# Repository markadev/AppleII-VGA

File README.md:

# Apple II VGA Card

This project is a VGA card for Apple II computers to ouput a crisp RGB signal to a
VGA monitor instead of having to rely on the composite output. This is accomplished
by snooping the 6502 bus and creating a shadow copy of the video memory within a
Raspberry Pi Pico, then processing the raw video memory contents to output a "perfect"
signal.

    +------+                +-----+      +-----------+
    | 6502 |________________| RAM |______| Composite | 
    | CPU  |  System   \    +-----+      | Video Gen |
    +------+   Bus     |                 +-----------+
                       |    +-----------+
                       \____| Raspberry |_________________\
                            |  Pi Pico  |   640x480 VGA   /
                            +-----------+

These features are currently supported:
 * Generates a 640x480@60 VGA signal with 3 bits per color channel using resistor DACs
 * Text mode (monochrome)
 * Lo-res mode with no color fringing between the chunky pixels
 * Hi-res mode with simulated NTSC artifact color
 * Mixed lo-res and hi-res modes with monochrome text and no color fringing
 * Apple IIe video modes: 80-column text, double-lores, & double-hires
   (thanks to @dkgrizzly and @Paco1979)
 * Soft-monochrome mode to force display as if on a monochrome monitor
 * Some Video-7 RGB card extended graphical modes are implemented
 * Compatibility with Videx VideoTerm modes on Apple II+ (thanks to @abaffa)

I had these goals in mind during design:
 * Generate video out to a more modern display - I don't have any old CRTs for
   displaying composite signals any more and composite to HDMI adapters don't work well.
 * Generate crisp video - I wanted "perfect" video output, the way that it should have
   been barring technical difficulties of displays in 1980. So like, no NTSC artifact
   coloring where it's not supposed to be.
 * Non-invasive - I didn't want to have to solder or modify my logic board.
 * Common parts - The parts to build should be cheap and easy to get anywhere,
   just like the original Apple II
 * Open-source - If this helps anyone else make their Apple II better then that's
   a bonus.

I also wanted to see if a Pi Pico could actually work on an 8-bit CPU bus, since the docs
say it should work but there were no code examples.

## Project Status

This is currently a DIY project that several folks have built on their own, ranging from
[hand-wired prototype boards](docs/prototype_card.jpg) to
[custom](https://user-images.githubusercontent.com/7944844/243266290-d05ce815-0a3d-4464-a4da-49dd44d71e92.jpg)
[PCBs](https://user-images.githubusercontent.com/94628/253134471-0d5ad359-75ae-400a-acfa-885c80c36e78.jpg)
and run in their Apple II+'s and IIe's. I consider it to be pretty stable at this point.

Included in this repo are:
 * The main expansion board [KiCad Project](AppleVGA/), [Schematics](AppleVGA/AppleVGA.pdf),
   [BOM](AppleVGA/AppleVGA_BOM.csv), and [Gerber files](AppleVGA/outputs/)
 * An optional connector board [KiCad Project](AppleVGA-Connector/),
   [Schematics](AppleVGA-Connector/AppleVGA-Connector.pdf),
   [BOM](AppleVGA-Connector/AppleVGA-Connector_BOM.csv),
   and [Gerber files](AppleVGA-Connector/outputs/). (You could also build a custom cable instead)
 * The [source code for the Pi Pico microcontroller](pico/)

If you're going to build a card then check the [assembly guide](docs/Assembly.md) and
[hardware changelog](AppleVGA/CHANGELOG.txt) for important notes.

Many thanks go to the folks in the Discussion area to help push this project forward with bug
fixes & reports, and design ideas!

**Main board**

**Connector board**
_thanks to @swetland for [this idea](https://github.com/markadev/AppleII-VGA/discussions/15#discussioncomment-6432841)_

**In the wild**

## Comparisons

Here are a few comparisons of the VGA card output vs composite video through
a cheap composite -> HDMI adapter

**Text**

**Lores**

**Hires**

**DHires**

**80 Columns**

## 80 Column support for the Apple II+

The firmware implements Videx VideoTerm compatibility when there's a VideoTerm card installed
in slot 3. It's not enabled by default but if you have a Videx VideoTerm card in slot 3
then you can enable 80 column VGA support using the Configuration Disk image. The VGA card
can still be installed in any slot.

**Apple II+ running 80 Columns Examples**

## Future work

With the Rev B hardware design, the firmware has access to the Apple bus' SYNC signal
when installed in slot 7. Theoretically the firmware could synchronize the VGA display
scans with the video hardware in the Apple II.

Though possible, it looks like it would be a large overhaul to implement this synchronization
and I've found no real-world use for it so I don't plan on completing this functionality.

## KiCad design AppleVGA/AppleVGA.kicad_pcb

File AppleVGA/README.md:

# AppleII-VGA expansion card

Requirements:
  - KiCad 8.0 or later

This project uses additional KiCad libraries:
 - https://github.com/ncarandini/KiCad-RP-Pico

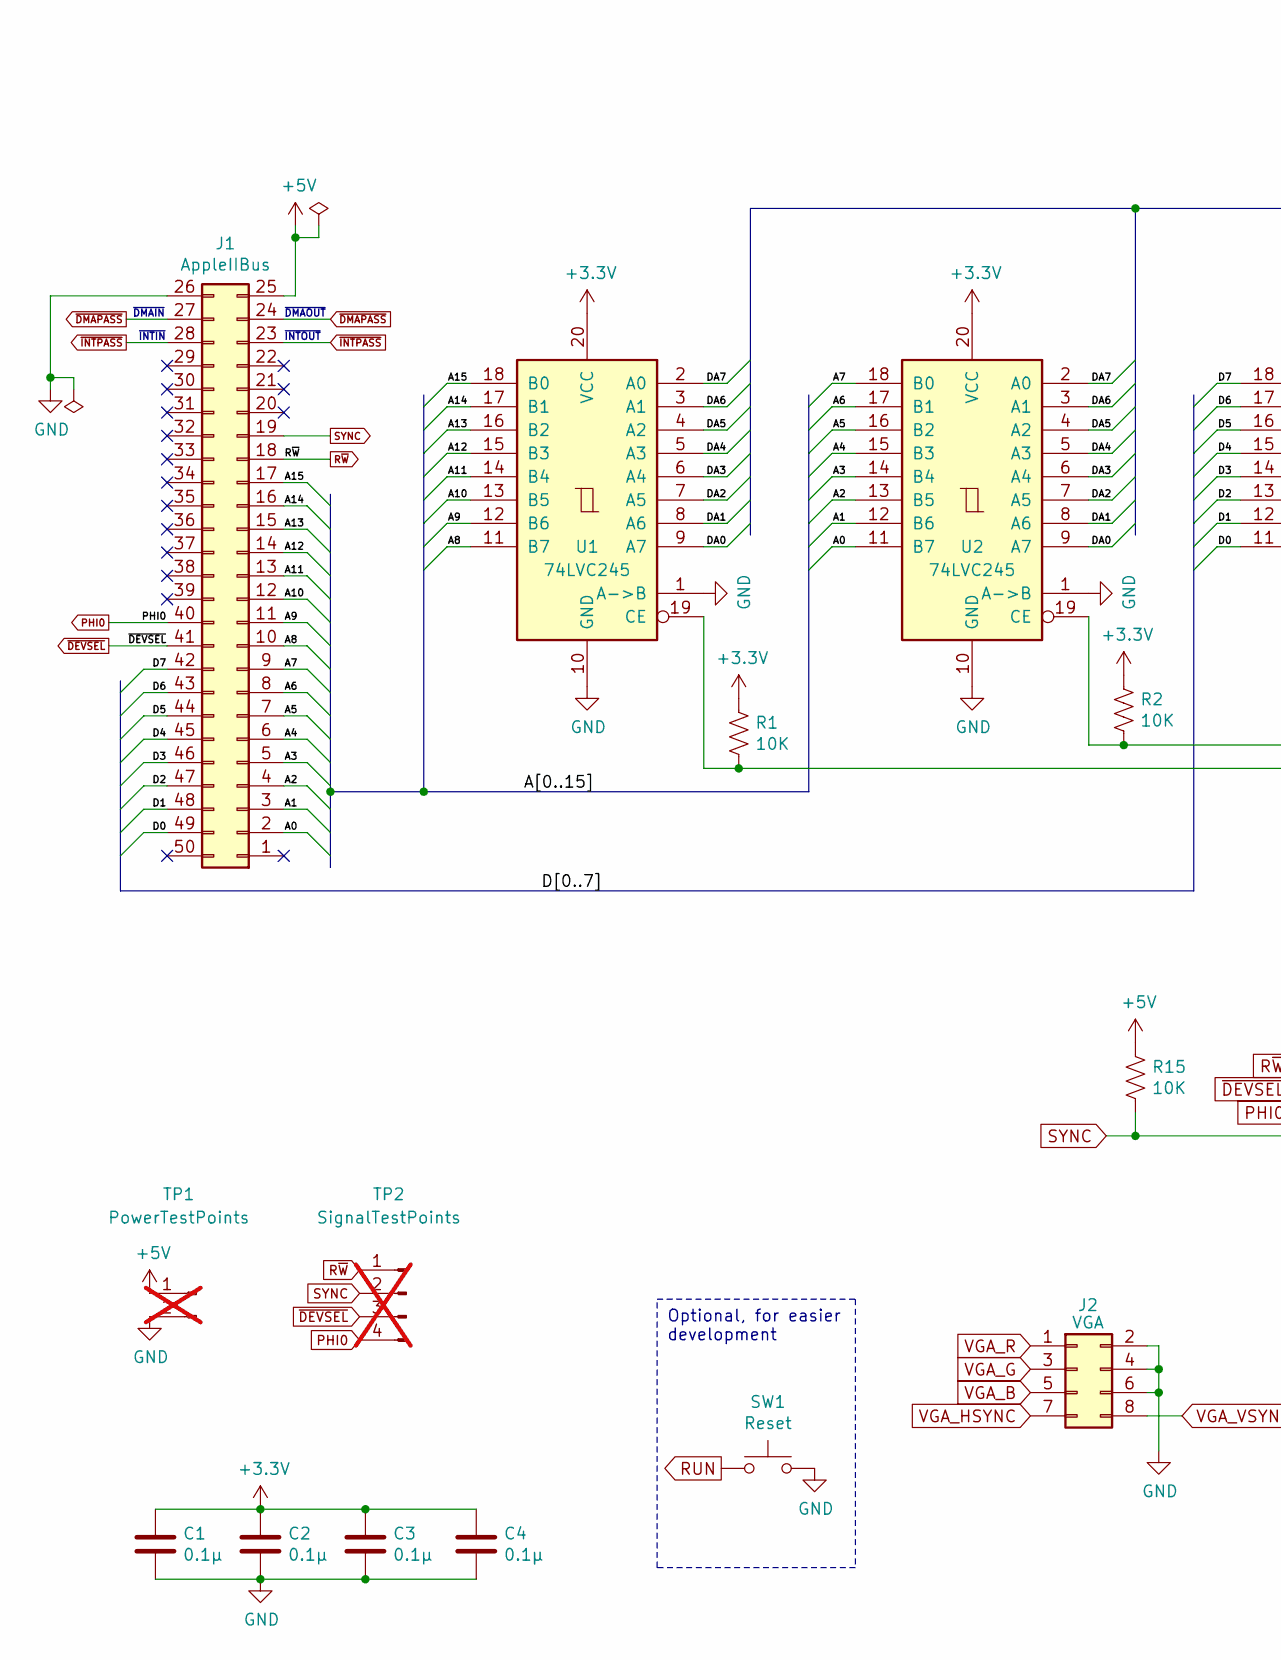
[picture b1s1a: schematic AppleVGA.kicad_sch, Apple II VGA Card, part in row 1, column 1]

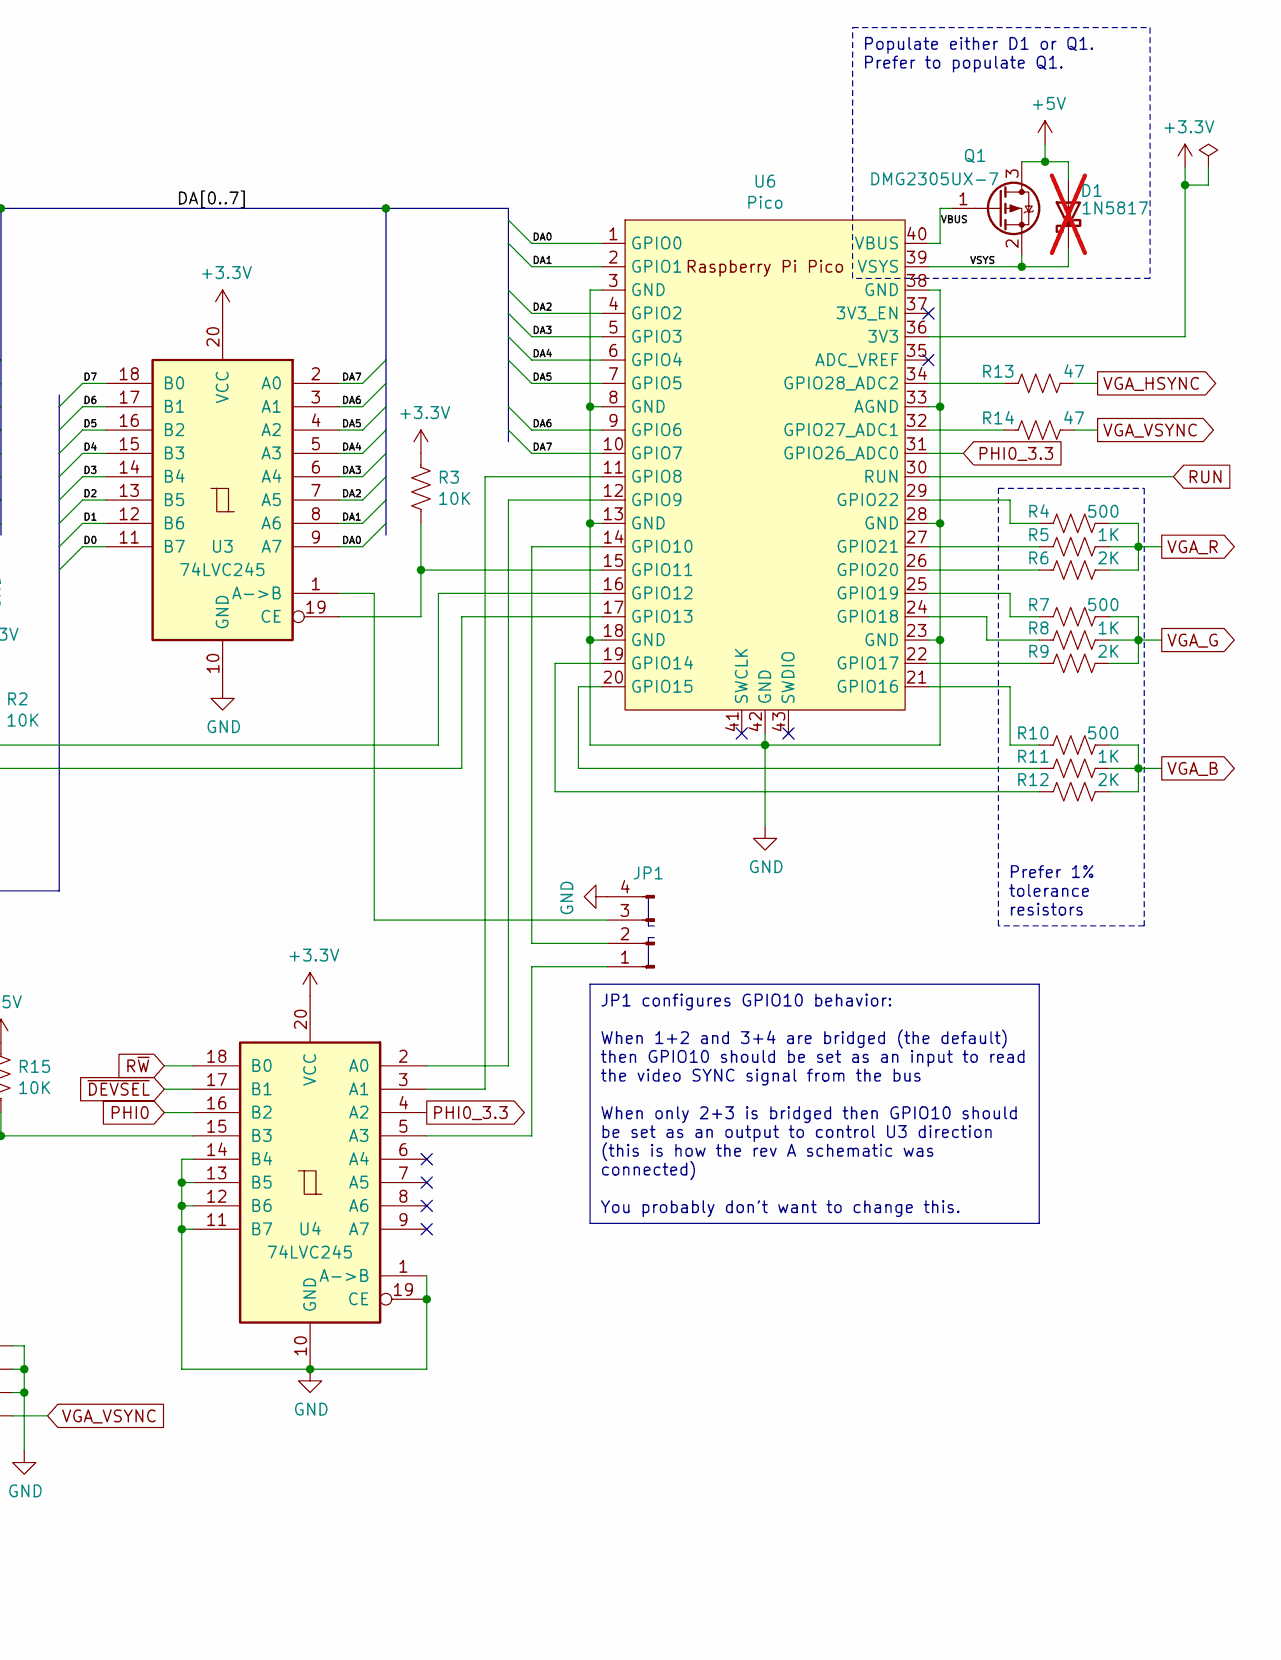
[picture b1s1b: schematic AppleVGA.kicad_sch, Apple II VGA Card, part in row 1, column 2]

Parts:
C1, C2, C3, C4: 0.1μ; C_Disc_D4.3mm_W1.9mm_P5.00mm; MouserNo 594-A104K15X7RF5TAA
D1: 1N5817; D_DO-41_SOD81_P10.16mm_Horizontal; MouserNo 511-1N5817; not fitted
J1: AppleIIBus; AppleIIBus_Edge
J2: VGA; IDC-Header_2x04_P2.54mm_Vertical; MouserNo 649-75869-232LF
JP1: JumperPads; SolderJumper-4_P1.3mm_Bridged12_34_RoundedPad1.0x1.5mm_Numb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
Q1: DMG2305UX-7; SOT-23; MouserNo 621-DMG2305UX-7
R1, R2, R3, R15: 10K; R_Axial_DIN0207_L6.3mm_D2.5mm_P10.16mm_Thin_Horizontal; MouserNo 603-CFR-25JR-5210K
R4, R7, R10: 500; R_Axial_DIN0207_L6.3mm_D2.5mm_P10.16mm_Thin_Horizontal; MouserNo 603-MFR-25FBF52-499R
R5, R8, R11: 1K; R_Axial_DIN0207_L6.3mm_D2.5mm_P10.16mm_Thin_Horizontal; MouserNo 603-MFR-25FBF52-1K
R6, R9, R12: 2K; R_Axial_DIN0207_L6.3mm_D2.5mm_P10.16mm_Thin_Horizontal; MouserNo 603-MFR-25FBF52-2K
R13, R14: 47; R_Axial_DIN0207_L6.3mm_D2.5mm_P10.16mm_Thin_Horizontal; MouserNo 603-MFR-25FTF52-47R
SW1: Reset; SW_PUSH_6mm_H5mm; MouserNo 506-FSM4JH
TP1: PowerTestPoints; PinHeader_1x02_P2.54mm_Vertical; not fitted
TP2: SignalTestPoints; PinHeader_1x04_P2.54mm_Vertical; not fitted
U1, U2, U3, U4: 74LVC245; DIP-20_W7.62mm_Socket; MouserNo 595-SN74LVC245AN
U6: Pico; RPi_Pico_SMD_TH

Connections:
+3.3V: C1.1, C2.1, C3.1, C4.1, R1.1, R2.1, R3.1, U1.20 (VCC), U2.20 (VCC), U3.20 (VCC), U4.20 (VCC), U6.36 (3V3)
+5V: D1.2 (A), J1.25, Q1.3 (D), R15.1, TP1.1
/A0: J1.2, U2.11 (B7)
/A1: J1.3, U2.12 (B6)
/A2: J1.4, U2.13 (B5)
/A3: J1.5, U2.14 (B4)
/A4: J1.6, U2.15 (B3)
/A5: J1.7, U2.16 (B2)
/A6: J1.8, U2.17 (B1)
/A7: J1.9, U2.18 (B0)
/A8: J1.10, U1.11 (B7)
/A9: J1.11, U1.12 (B6)
/A10: J1.12, U1.13 (B5)
/A11: J1.13, U1.14 (B4)
/A12: J1.14, U1.15 (B3)
/A13: J1.15, U1.16 (B2)
/A14: J1.16, U1.17 (B1)
/A15: J1.17, U1.18 (B0)
/D0: J1.49, U3.11 (B7)
/D1: J1.48, U3.12 (B6)
/D2: J1.47, U3.13 (B5)
/D3: J1.46, U3.14 (B4)
/D4: J1.45, U3.15 (B3)
/D5: J1.44, U3.16 (B2)
/D6: J1.43, U3.17 (B1)
/D7: J1.42, U3.18 (B0)
/DA0: U1.9 (A7), U2.9 (A7), U3.9 (A7), U6.1 (GPIO0)
/DA1: U1.8 (A6), U2.8 (A6), U3.8 (A6), U6.2 (GPIO1)
/DA2: U1.7 (A5), U2.7 (A5), U3.7 (A5), U6.4 (GPIO2)
/DA3: U1.6 (A4), U2.6 (A4), U3.6 (A4), U6.5 (GPIO3)
/DA4: U1.5 (A3), U2.5 (A3), U3.5 (A3), U6.6 (GPIO4)
/DA5: U1.4 (A2), U2.4 (A2), U3.4 (A2), U6.7 (GPIO5)
/DA6: U1.3 (A1), U2.3 (A1), U3.3 (A1), U6.9 (GPIO6)
/DA7: U1.2 (A0), U2.2 (A0), U3.2 (A0), U6.10 (GPIO7)
/VBUS: Q1.1 (G), U6.40 (VBUS)
/VSYS: D1.1 (K), Q1.2 (S), U6.39 (VSYS)
GND: C1.2, C2.2, C3.2, C4.2, J1.26, J2.2, J2.4, J2.6, JP1.4, SW1.2, TP1.2, U1.1 (A->B), U1.10 (GND), U2.1 (A->B), U2.10 (GND), U3.10 (GND), U4.1 (A->B), U4.10 (GND), U4.11 (B7), U4.12 (B6), U4.13 (B5), U4.14 (B4), U4.19 (CE), U6.3 (GND), U6.8 (GND), U6.13 (GND), U6.18 (GND), U6.23 (GND), U6.28 (GND), U6.33 (AGND), U6.38 (GND), U6.42 (GND)
unnamed: JP1.1, U4.5 (A3)
unnamed: JP1.2, U6.14 (GPIO10)
unnamed: JP1.3, U3.1 (A->B)
unnamed: R1.2, U1.19 (CE), U6.17 (GPIO13)
unnamed: R2.2, U2.19 (CE), U6.16 (GPIO12)
unnamed: R3.2, U3.19 (CE), U6.15 (GPIO11)
unnamed: U4.2 (A0), U6.12 (GPIO9)
unnamed: U4.3 (A1), U6.11 (GPIO8)
unnamed: R12.1, U6.19 (GPIO14)
unnamed: R11.1, U6.20 (GPIO15)
unnamed: R10.1, U6.21 (GPIO16)
unnamed: R9.1, U6.22 (GPIO17)
unnamed: R8.1, U6.24 (GPIO18)
unnamed: R7.1, U6.25 (GPIO19)
unnamed: R6.1, U6.26 (GPIO20)
unnamed: R5.1, U6.27 (GPIO21)
unnamed: R4.1, U6.29 (GPIO22)
unnamed: R14.1, U6.32 (GPIO27_ADC1)
unnamed: R13.1, U6.34 (GPIO28_ADC2)
PHI0: J1.40, TP2.4, U4.16 (B2)
PHI0_3.3: U4.4 (A2), U6.31 (GPIO26_ADC0)
RUN: SW1.1, U6.30 (RUN)
R~W: J1.18, TP2.1, U4.18 (B0)
SYNC: J1.19, R15.2, TP2.2, U4.15 (B3)
VGA_B: J2.5, R10.2, R11.2, R12.2
VGA_G: J2.3, R7.2, R8.2, R9.2
VGA_HSYNC: J2.7, R13.2
VGA_R: J2.1, R4.2, R5.2, R6.2
VGA_VSYNC: J2.8, R14.2
~DEVSEL: J1.41, TP2.3, U4.17 (B1)
~DMAPASS: J1.24, J1.27
~INTPASS: J1.23, J1.28

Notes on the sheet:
Optional, for easier development
Populate either D1 or Q1. Prefer to populate Q1.
JP1 configures GPIO10 behavior: When 1+2 and 3+4 are bridged (the default) then GPIO10 should be set as an input to read the video SYNC signal from the bus When only 2+3 is bridged then GPIO10 should be set as an output to control U3 direction (this is how the rev A schematic was connected) You pro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
Prefer 1% tolerance resistors
~{DMAIN}
~{INTOUT}
~{DMAOUT}
~{INTIN}

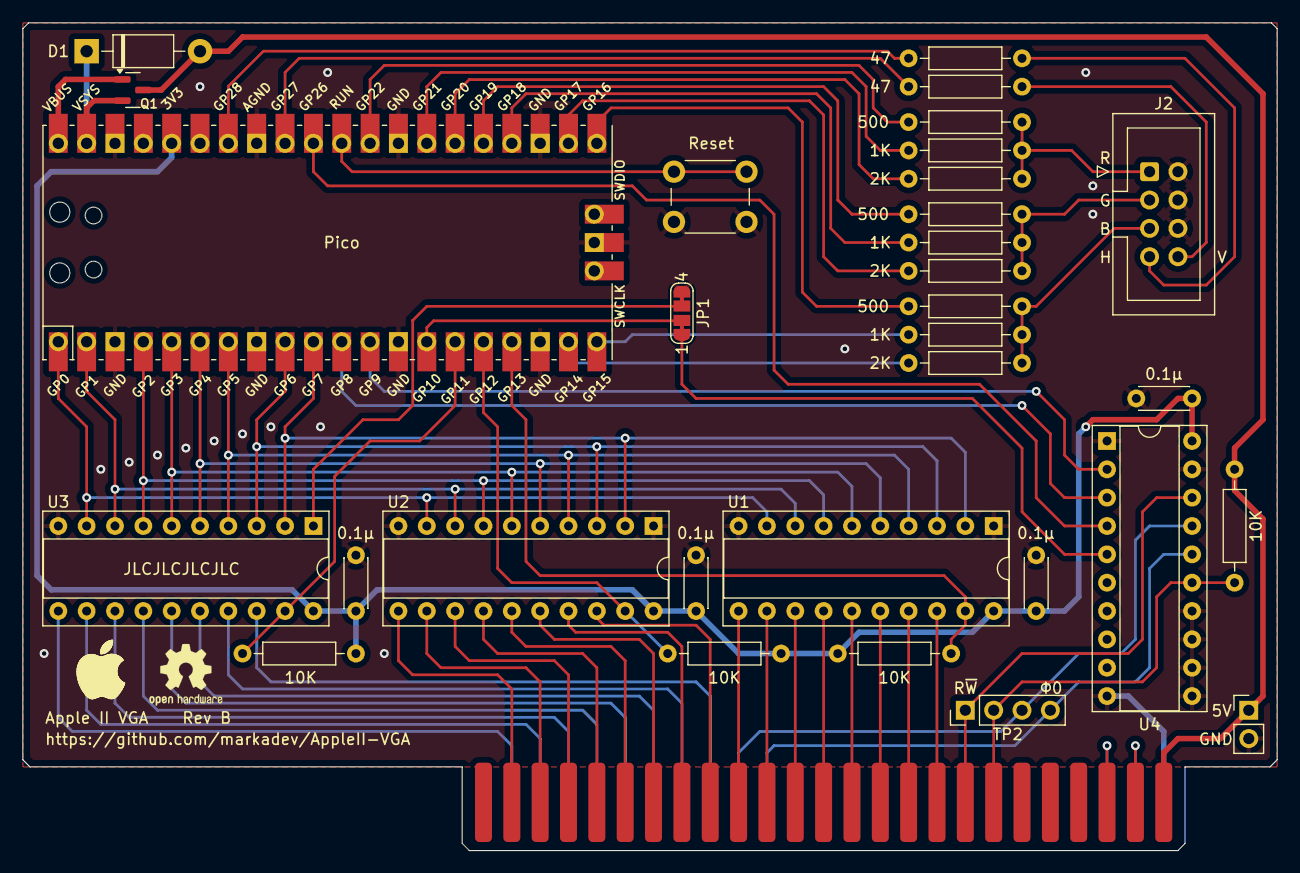
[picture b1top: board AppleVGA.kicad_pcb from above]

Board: 2 copper layers, 112.4 x 74.2 mm, 33 parts (0 on the bottom side), 69 nets.

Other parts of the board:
LOGO1: AppleLogo_5mm

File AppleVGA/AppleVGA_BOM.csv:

"#","Reference","Qty","Value","Footprint","DNP","Mfr","MfrNo","MouserNo"
"1","C1, C2, C3, C4","4","0.1μ","Capacitor_THT:C_Disc_D4.3mm_W1.9mm_P5.00mm","","","","594-A104K15X7RF5TAA"
"2","D1","1","1N5817","Diode_THT:D_DO-41_SOD81_P10.16mm_Horizontal","DNP","STMicroelectronics","1N5817","511-1N5817"
"3","J2","1","VGA","Connector_IDC:IDC-Header_2x04_P2.54mm_Vertical","","","","649-75869-232LF"
"4","Q1","1","DMG2305UX-7","Package_TO_SOT_SMD:SOT-23","","Diodes Incorporated","DMG2305UX-7","621-DMG2305UX-7"
"5","R1, R2, R3, R15","4","10K","AppleVGA:R_Axial_DIN0207_L6.3mm_D2.5mm_P10.16mm_Thin_Horizontal","","","","603-CFR-25JR-5210K"
"6","R4, R7, R10","3","500","AppleVGA:R_Axial_DIN0207_L6.3mm_D2.5mm_P10.16mm_Thin_Horizontal","","","","603-MFR-25FBF52-499R"
"7","R5, R8, R11","3","1K","AppleVGA:R_Axial_DIN0207_L6.3mm_D2.5mm_P10.16mm_Thin_Horizontal","","","","603-MFR-25FBF52-1K"
"8","R6, R9, R12","3","2K","AppleVGA:R_Axial_DIN0207_L6.3mm_D2.5mm_P10.16mm_Thin_Horizontal","","","","603-MFR-25FBF52-2K"
"9","R13, R14","2","47","AppleVGA:R_Axial_DIN0207_L6.3mm_D2.5mm_P10.16mm_Thin_Horizontal","","","","603-MFR-25FTF52-47R"
"10","SW1","1","Reset","Button_Switch_THT:SW_PUSH_6mm_H5mm","","TE Connectivity","FSM4JH","506-FSM4JH"
"11","U1, U2, U3, U4","4","74LVC245","Package_DIP:DIP-20_W7.62mm_Socket","","TI","SN74LVC245AN","595-SN74LVC245AN"
"12","U6","1","Pico","MCU_RaspberryPi_and_Boards:RPi_Pico_SMD_TH","","","",""

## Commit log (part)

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2021-11-10 Initial commit of pico source skeleton
2021-11-13 Add first pass at VGA PIO state machines
2021-11-13 Add a simple VGA test pattern
    It works! but the data FIFO isn't being filled fast enough.
2021-11-14 Fix horizontal pixel jitter
    Use DMA to write the test scanlines to avoid FIFO underruns
    and adjust the timings to remove jitter caused by the
    fractional clock dividers.
2021-11-14 Fix missing first column of pixels
2021-11-14 Add cheap pixel doubling/tripling/quadrupling and allow the next scanline to be built while the current one is being DMA'd
2021-11-16 Move rendering code to render.c and measure the render time with a spare GPIO
2021-11-16 Use default cmake languages
2021-11-17 use 32-bit DMA transfers for VGA pixel data
2021-11-18 Add async triggering of the next scanline buffer from an irq handler
2021-11-18 Move test pattern rendering into a separate function
2021-11-27 Fix a comment
2021-11-27 Clean up VGA frame setup
2021-12-18 Initial Apple II bus interface
2021-12-25 Fix mapping of text line to memory address in textmode
2021-12-27 Fix abus to work on a real Apple II bus.
    Set up text memory shadowing and fixed a few abus issues:
    * Keep input synchronizer enabled on the PHI0 clock because it
    messes up the PIO in weird ways.
    * Sample DEVSEL at an appropriate time within phase 0
    Text memory shadowing works now, as well as device read cycle handling
2021-12-27 Center the text mode in the VGA screen resolution
2022-01-01 Complete memory shadowing
    Add shadowing of text and hires memory plus the graphics mode soft-switches
2022-01-01 Add non-mixed lores mode
2022-01-01 Add placeholder for hires rendering, integrated with mixed-mode support
2022-01-01 Put the character ROM in RAM so it can be modified on the fly
2022-01-02 Add a README
2022-01-02 Add the schematics
2022-01-02 hires mode prototype
2022-01-04 Fix the reversed lores colors
2022-01-08 Create a better test pattern and tweak the lores colors
2022-01-08 Fix artifacts on the last column of hires pixels
2022-01-09 Tweak the hires interference pattern colors
2022-01-20 Don't latch in the PAGE2 value for an entire frame
    Check the PAGE2 soft-switch more frequently so that the 'inactive'
    page's content won't be rendered sooner after a page flip happens.
    This resolves the flickering in Choplifter
2022-01-25 Add some images from the prototype
2022-01-25 Add future work
2022-08-31 Bill Of Materials CSV added
2022-09-08 Error fix: Input Power pin not driven by Output Powers pins
2022-09-26 Pico README added
2023-06-10 Backport a small lores optimization
    Backport longer pixel fill operations from the V2 Analog project
    along with its use to simplify lores rendering.
    Copyright (c) David Kuder (https://github.com/V2RetroComputing/analog-firmware)
2023-06-10 Update the lores palette
    Use the lores palette that the Apple IIGS uses, which more
    closely resembles the composite color output - especially
    the magenta/red color.
2023-06-20 Update pico_sdk_import.cmake from current pico-sdk
2023-06-21 Add tentative clang-format configuration
    Initial clang-format configuration that is as close to the
    current formatting as I think it can be.
2023-06-22 Working modes, expect for KQ1 lol
2023-06-22 Added Reset handling and video 7 soft switch tricks
2023-06-22 Functioning Double High Res (King Quest 1 WORKS!)
2023-06-22 Made video7 magic more understandable
2023-06-22 Fixed magical video 7 soft switch
2023-06-22 use HTML color codes to twick the pallet, fixed Reset memory clearing
2023-06-22 made all formating changes
2023-06-22 Added #ifdef APPLE_MODEL_IIE
2023-06-22 Updated format and fixed apple ii+ bug
2023-06-22 fixed white spaces and missing lores_dot_patterns.h files
2023-06-23 Fixed MR issues
2023-06-23 Updated documentation
2023-06-30 Minor README tweaks
2023-07-01 Move the test pattern rendering into a new .c file
2023-07-01 II+ text font fixes
    Justify the characters at the bottom of the text cell to be true
    to the original. The IIe justifies them at the top so the lower-case
    characters can dip down lower.
    Also fix the '3' and '"' characters.
2023-07-01 IIe font fixes
    Fixed the '3' and '"' characters in the IIe font.
2023-07-02 Refactor soft-switch dispatching
    Using a table of functions so the execution time is O(1) for all soft-switch
    accesses. This squashes an 800ns processing time outlier when idling at the
    Basic prompt back down into the 200-300ns range.
2023-07-03 Fix a bug in double-hires mode selection
    Fix a bug where an incorrect video7 mode could be selected.
    I updated the 80COL/AN3 softswitch logic to more closely follow
    what's described in patent US4631692.
    The MODETEST test for double-hires now passes more reliably and
    King's Quest didn't break :D
2023-07-03 Fix aux memory write inconsistencies
    Fix the detection of writes to AUX memory so that it's consistent
    with a real IIe when various combinations of soft-switches are set.
    The BANKTEST results now match the real machine.
2023-07-04 Remove IOUDIS shadowing
    The value wasn't used anywhere and I confirmed on a real IIe that it doesn't
    seem to affect setting AN3 like some notes on the internet suggested.
2023-07-04 Replace a bunch of binary enums with bool types
2023-07-05 Cleaner double-lores output
    Simplify the double-lores rendering to remove the simulated artifacting so
    it's nice clean chunky pixels, like lores mode.
2023-07-05 Remove superfluous 'right padding' pixels
2023-07-09 Increase double-hires mode switch accuracy
    Update the double-hires mode soft-soft check to be more accurate to
    what I measured on my read IIe. Double-hires only seems to get enabled
    when both 80COL and DHIRES are set.
2023-07-13 Fix a comment and some formatting
2023-07-16 Remove Video-7 foreground/background hires
    Remove the Video-7 foreground/background hires codes from the double-hires
    rendering. According to the Video-7 User Manual section 7.5, this is a HIRES
    mode and the Apple //e must be in HIRES mode to activate it, so it shouldn't
    be in the double-hires rendering.
2023-07-16 Experiment with alternate text color support
2023-07-16 Mess around with simulating scanlines
2023-07-24 Clean up duplicate hires mode checks
    Merge render_hires and render_hires_mixed to get rid of the
    duplicate mode checks that each one is doing.
2023-07-24 Optimize dhires mixed mono/color mode to fix some jitter
2023-07-25 Fix rendering artifacts in video-7 mixed mode (pt.1)
    Rewrote most of the mixed video-7 rendering code to properly handle
    when the 'mode' changes in bytes that don't align with the 4-bit dhires
    pixel color codes.
    It resolves the artifacts I see in the AppleColor demo disk progams,
    but is currently too slow to render the entire screen in time.
2023-07-28 Make current monochrome modes consistent
    Make the currently implemented monochrome modes consistently get enabled when
    the soft_monochrom soft-switch is set and also make the use of the monochrome
    mode colors consistent across the current renderers.
2023-07-29 Add monochrome rendering for dlores mode
2023-07-29 Add a couple RGB constants for future testing
2023-07-30 No-op variable name cleanup
    Update some var names in the dhires rendering code to be consistent with
    the other mode renderers.
2023-07-30 Move the page2 rendering decision logic into a function
2023-07-30 Add comments & refs for the palette definitions
2023-07-30 Minor optimization to dhires rendering
2023-09-09 Remove read_cycle support
    I'm removing support for the firmware to be able to put data on the data
    bus in response to a device read cycle. The GPIO currently connected to
    the Data transceiver direction will be hard-coded as an input pulled low
    to preserve compatibility with the current (rev A) schematic.
    I originally intended to use this to add Videx card emulation but have
    abandoned that idea because:
2023-09-09 Formatting fix
2023-09-10 Add a register to choose colors in soft-monochrome mode
2023-09-17 Check in the KiCad project for the connector board
2023-09-17 wordsmith
2023-09-30 Update picture with better lighting and focus
2023-09-30 Add a note about the hex standoffs
2023-11-30 Refactor the character ROM and text rendering
    Rewrite the text character rendering to use a character ROM format similar to
    original Apple II video ROMs so that original ROM data could be used more easily.
2023-12-10 Improve reset detection
    Mimic the algorithm that the Apple IIe IOU chips uses to detect
    CPU resets from bus activity to reduce the possibility of false
    positives even more.
2023-12-29 Create textfont_iiplus_lower.c
    Contains Videx Lowercase ROM characters for the II+
2023-12-30 Configure without POKE commands. The utility is within startup.bas in the AppleIIVGAUTIL.dsk file and will start when the disk is loaded. Write it to a physical disk using ADTPro, or another similar 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
2024-01-01 Apple II Plus Lowercase Character Set Support (#29)
    * Create textfont_iiplus_lower.c
    Contains Videx Lowercase ROM characters for the II+
    * Added Apple II+ lowercase character ROM in alternative textfont* file and new cmake variant for IIPLUSLC. Updated Readme.MD with instructions for building firmware using cmake variant created (IIPL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
2024-01-11 Place all code/data to RAM by default
    Configure the build to place all code and data into RAM instead of flash by default.
    Then remove all the __time_critical_func decorators that were trying to do this but
    not fully covering all the important code.
    The default character ROM will remain in flash since it's only read once at startup.
    This will allow program flash to be modified without having to perform complex cross-core
    synchronization to stop flash accesses.
2024-01-13 Move the VGA card's custom register logic into device_regs.c
2024-01-13 Add register 0x04 for device commands
2024-01-13 Add command for (re)loading a character ROM
    Start adding support for switching between standard character ROMs by
    adding a command to load 1 of 16 in-built ROMs.
    Now instead of having a separate built variant for II+ lower-case text,
    both the normal and lower-case fonts are built-in and can be switched
    with a register setting.
2024-01-15 Add several standard IIe character sets
2024-01-15 Add a Makefile to build the configurator disk
2024-01-15 Update the config program with new options and flash save support
2024-01-17 Update AppleCommander version
2024-01-27 Fix a typo in the firmware README
2024-02-08 . adding support to Reading registers/firmware (need overclock) . adding support to videx card on slot 3 . adding videx text fonts
2024-02-08 updating README.md
2024-02-08 . adding 80 mode examples to README.md
2024-02-08 Update README.md
    adding videos to readme
2024-03-08 Integrate shadowing of Videx writes
    Refactored the original videx write handling to integrate it in
    with the existing shadow write tables and functions.
2024-03-08 Consolidate all the Videx VideoTerm code
2024-03-08 Small Videx rendering fix
    Calculate the text window's start address and cursor
    address one at the start of the rendering frame to limit
    scrolling artifacts.
2024-03-10 Add an enable flag for the Videx support
2024-03-15 Convert the AppleVGA-Connector KiCad project to KiCad 8
2024-06-11 Add option to always use the monochrome text color
    Add a configuration option so that the monochome text color will always used
    for full text modes. Mixed modes will still use black & white for text when
    soft-monochrome mode is not enabled so that color graphics won't be intermixed
    with green or amber text.
2024-11-06 Fixes for pico-sdk 2.0.0 release
2025-11-23 Make hires rendering more similar to dhires
    Refactor the hires rendering to work more like the dhires rendering,
    which uses an in-memory bitmap from LSB to MSB to represent the video
    dots.
    Updated the hires color pattern generation with better "interference"
    colors, and added the rgb_filter_demo script to preview the result
    without having to load onto the VGA card.
2025-12-04 Add a smooth hires color table
    Add a second color table for hires rendering that smooths transitions
    between colors more like a composite monitor would.

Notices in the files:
AppleVGA/AppleVGA.kicad_pcb:
Licensed under CERN-OHL-P V2.0 (https://ohwr.org/cern_ohl_p_v2.txt)
Copyright (c) 2021-2023 Mark Aikens
